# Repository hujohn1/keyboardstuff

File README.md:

4-key wired macropad powered with USB-C

v1: Jul 28, 2026
Changed resistors from 5k to 5.1k
Added status LED
Changed multiple global labels to net labels
Rewired WS2812s
Changed resistor and capacitor namings

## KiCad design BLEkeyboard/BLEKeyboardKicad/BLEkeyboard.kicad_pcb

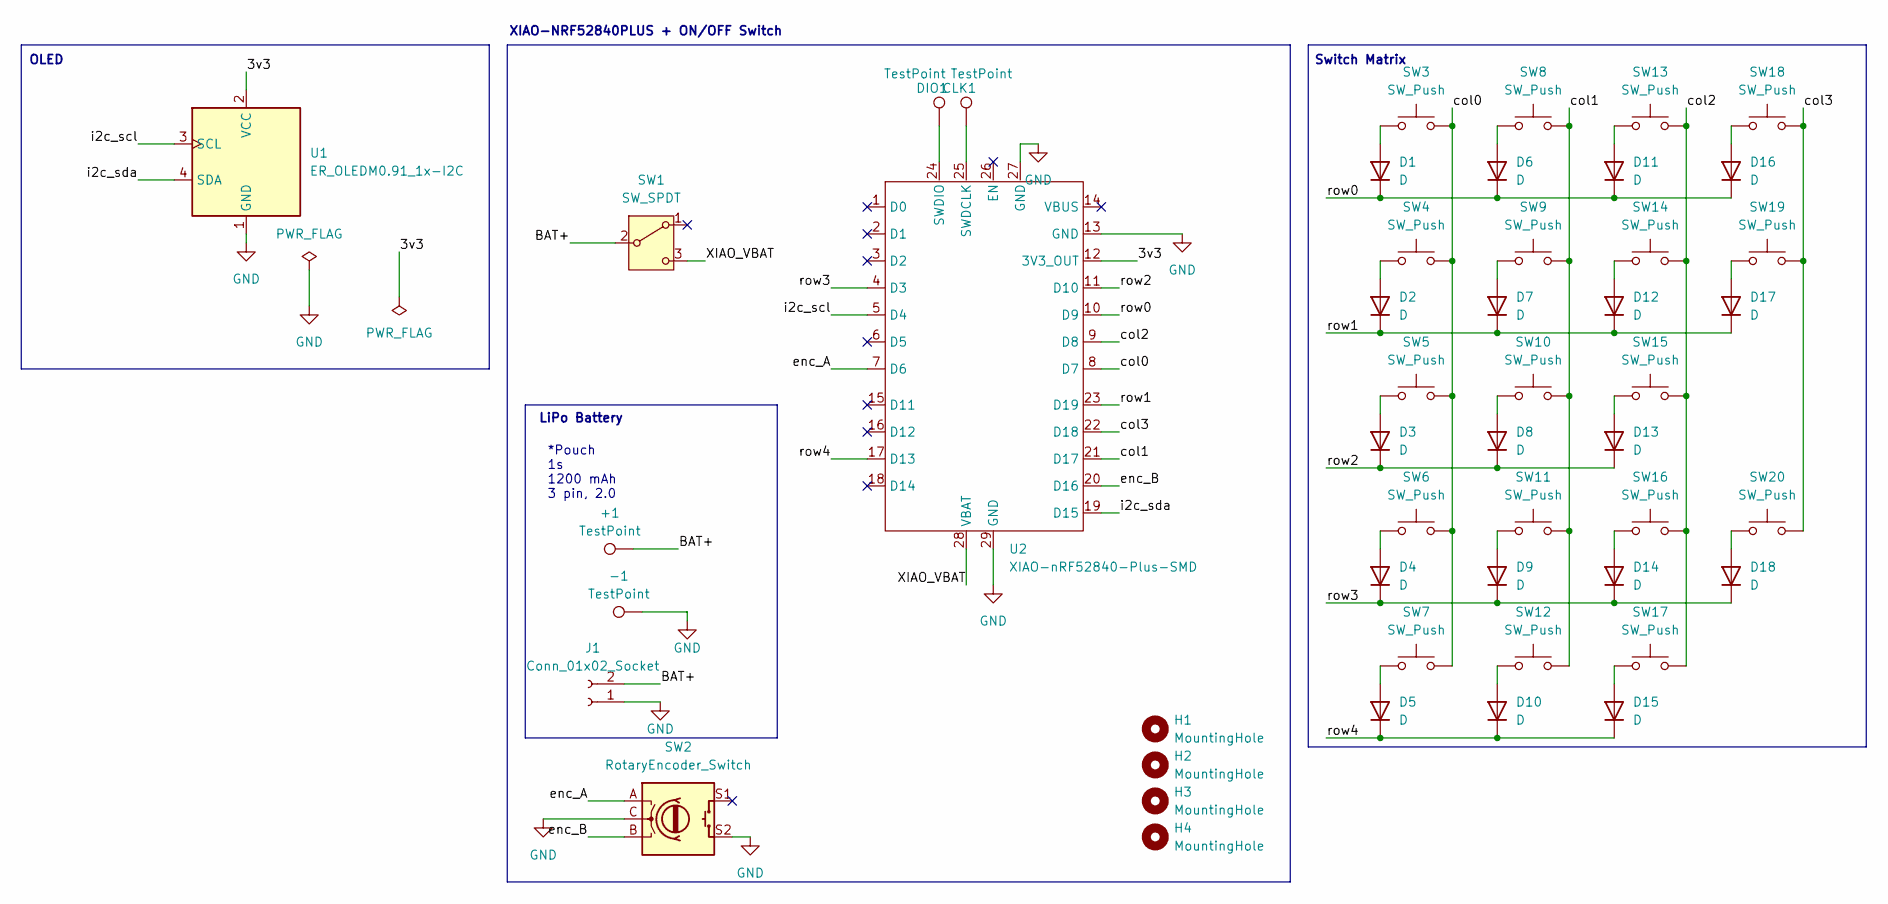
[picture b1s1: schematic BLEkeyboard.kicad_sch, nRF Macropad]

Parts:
+1: TestPoint; TestPoint_THTPad_D1.0mm_Drill0.5mm
-1: TestPoint; TestPoint_THTPad_D1.0mm_Drill0.5mm
CLK1: TestPoint; TestPoint_Pad_D2.0mm
D1, D2, D3, D4, D5, D6, D7, D8, D9, D10, D11, D12, D13, D14, D15, D16, D17, D18: D; D_DO-34_SOD68_P7.62mm_Horizontal
DIO1: TestPoint; TestPoint_Pad_D2.0mm
H1, H2, H3, H4: MountingHole; MountingHole_2.2mm_M2
J1: Conn_01x02_Socket; JST_PH_S2B-PH-K_1x02_P2.00mm_Horizontal
SW1: SW_SPDT; MK-12C02-G020_GSW
SW2: RotaryEncoder_Switch; RotaryEncoder_Alps_EC11E-Switch_Vertical_H20mm_MountingHoles
SW3, SW4, SW5, SW6, SW7, SW8, SW9, SW10, SW11, SW12, SW13, SW14, SW15, SW16, SW17, SW18: SW_Push; SW_Cherry_MX_PCB_1.00u
SW19, SW20: SW_Push; CherryMX_2.00u_PCB_StabWireBottom
U1: ER_OLEDM0.91_1x-I2C
U2: XIAO-nRF52840-Plus-SMD

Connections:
/3v3: U1.2 (VCC), U2.12 (3V3_OUT)
/BAT+: +1.1, J1.2, SW1.2 (B); also elsewhere on the board
/XIAO_VBAT: SW1.3 (C), U2.28 (VBAT)
/col0: SW3.2, SW4.2, SW5.2, SW6.2, SW7.2, U2.8 (D7)
/col1: SW8.2, SW9.2, SW10.2, SW11.2, SW12.2, U2.21 (D17)
/col2: SW13.2, SW14.2, SW15.2, SW16.2, SW17.2, U2.9 (D8)
/col3: SW18.2, SW19.2, SW20.2, U2.22 (D18)
/enc_A: SW2.A, U2.7 (D6)
/enc_B: SW2.B, U2.20 (D16)
/i2c_scl: U1.3 (SCL), U2.5 (D4)
/i2c_sda: U1.4 (SDA), U2.19 (D15)
/row0: D1.1 (K), D6.1 (K), D11.1 (K), D16.1 (K), U2.10 (D9)
/row1: D2.1 (K), D7.1 (K), D12.1 (K), D17.1 (K), U2.23 (D19)
/row2: D3.1 (K), D8.1 (K), D13.1 (K), U2.11 (D10)
/row3: D4.1 (K), D9.1 (K), D14.1 (K), D18.1 (K), U2.4 (D3)
/row4: D5.1 (K), D10.1 (K), D15.1 (K), U2.17 (D13)
GND: -1.1, J1.1, SW2.C, SW2.S2, U1.1 (GND), U2.13 (GND), U2.27 (GND), U2.29 (GND); also elsewhere on the board
unnamed: D1.2 (A), SW3.1
unnamed: D2.2 (A), SW4.1
unnamed: D3.2 (A), SW5.1
unnamed: D4.2 (A), SW6.1
unnamed: D5.2 (A), SW7.1
unnamed: D6.2 (A), SW8.1
unnamed: D7.2 (A), SW9.1
unnamed: D8.2 (A), SW10.1
unnamed: D9.2 (A), SW11.1
unnamed: D10.2 (A), SW12.1
unnamed: D11.2 (A), SW13.1
unnamed: D12.2 (A), SW14.1
unnamed: D13.2 (A), SW15.1
unnamed: D14.2 (A), SW16.1
unnamed: D15.2 (A), SW17.1
unnamed: D16.2 (A), SW18.1
unnamed: D17.2 (A), SW19.1
unnamed: D18.2 (A), SW20.1
unnamed 35: CLK1.1, U2.25 (SWDCLK); also elsewhere on the board
unnamed 36: DIO1.1, U2.24 (SWDIO); also elsewhere on the board

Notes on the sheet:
LiPo Battery
OLED
*Pouch 1s 1200 mAh 3 pin, 2.0
XIAO-NRF52840PLUS + ON/OFF Switch
Switch Matrix

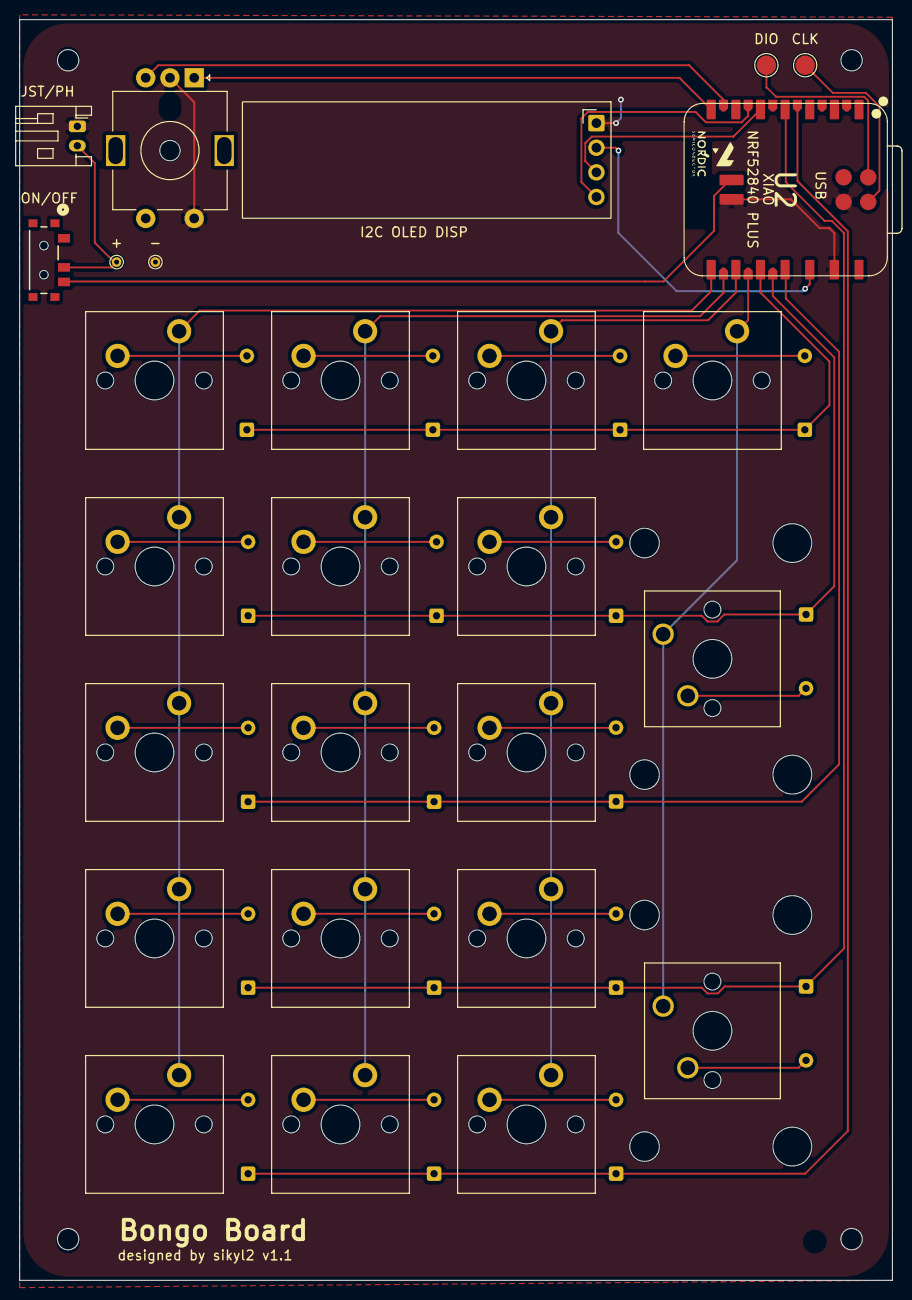
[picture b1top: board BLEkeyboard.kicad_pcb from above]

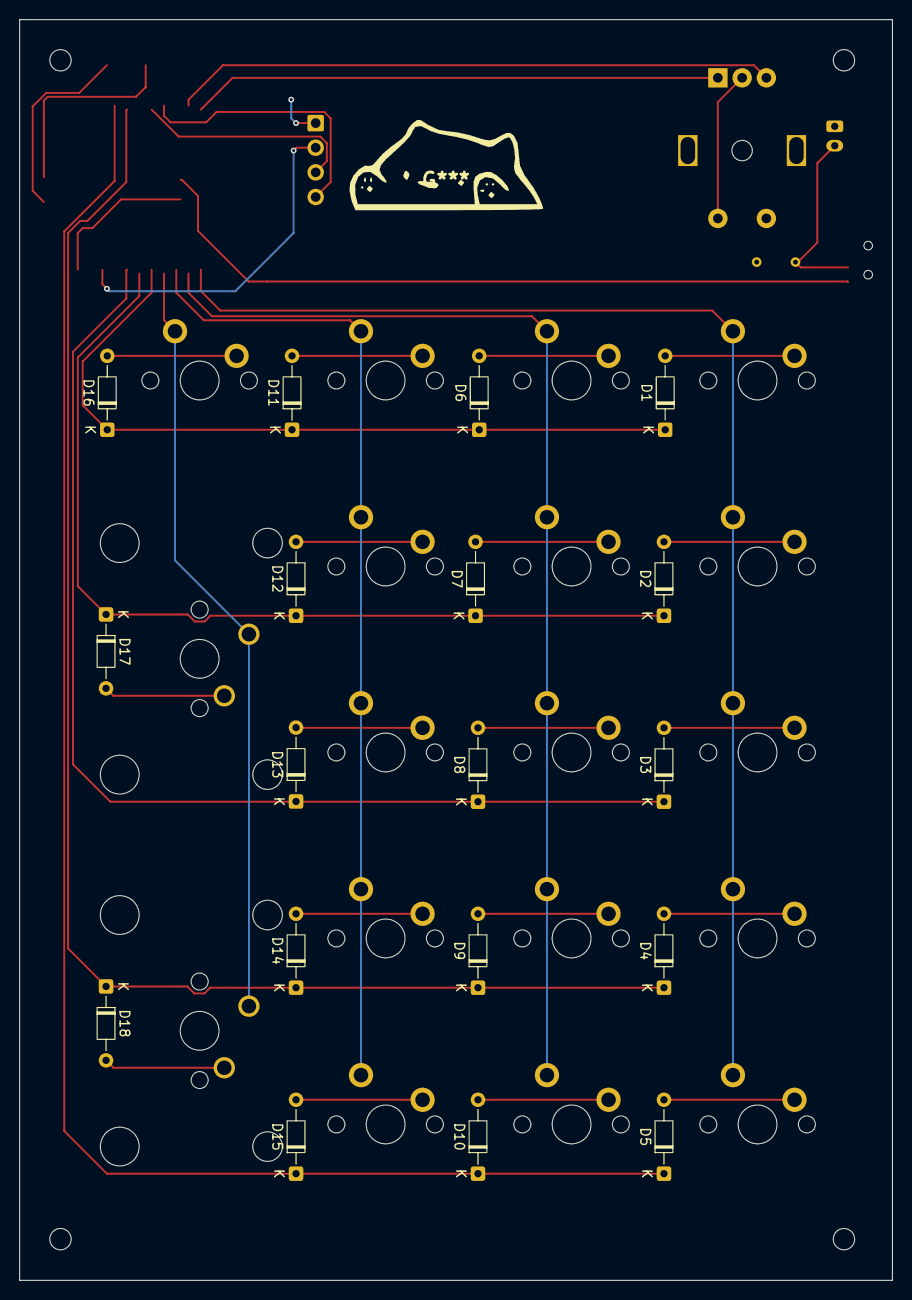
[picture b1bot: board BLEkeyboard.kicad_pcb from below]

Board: 2 copper layers, 90.0 x 130.0 mm, 50 parts (18 on the bottom side), 37 nets.

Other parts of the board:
': LOGO
+: TestPoint; TestPoint_THTPad_D1.0mm_Drill0.5mm
-: TestPoint; TestPoint_THTPad_D1.0mm_Drill0.5mm
CLK: TestPoint; TestPoint_Pad_D2.0mm
DIO: TestPoint; TestPoint_Pad_D2.0mm

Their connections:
/BAT+: +.1 (1_1); also elsewhere on the board
GND: -.1 (1_1); also elsewhere on the board
unnamed 35: CLK.1 (1_1); also elsewhere on the board
unnamed 36: DIO.1 (1_1); also elsewhere on the board

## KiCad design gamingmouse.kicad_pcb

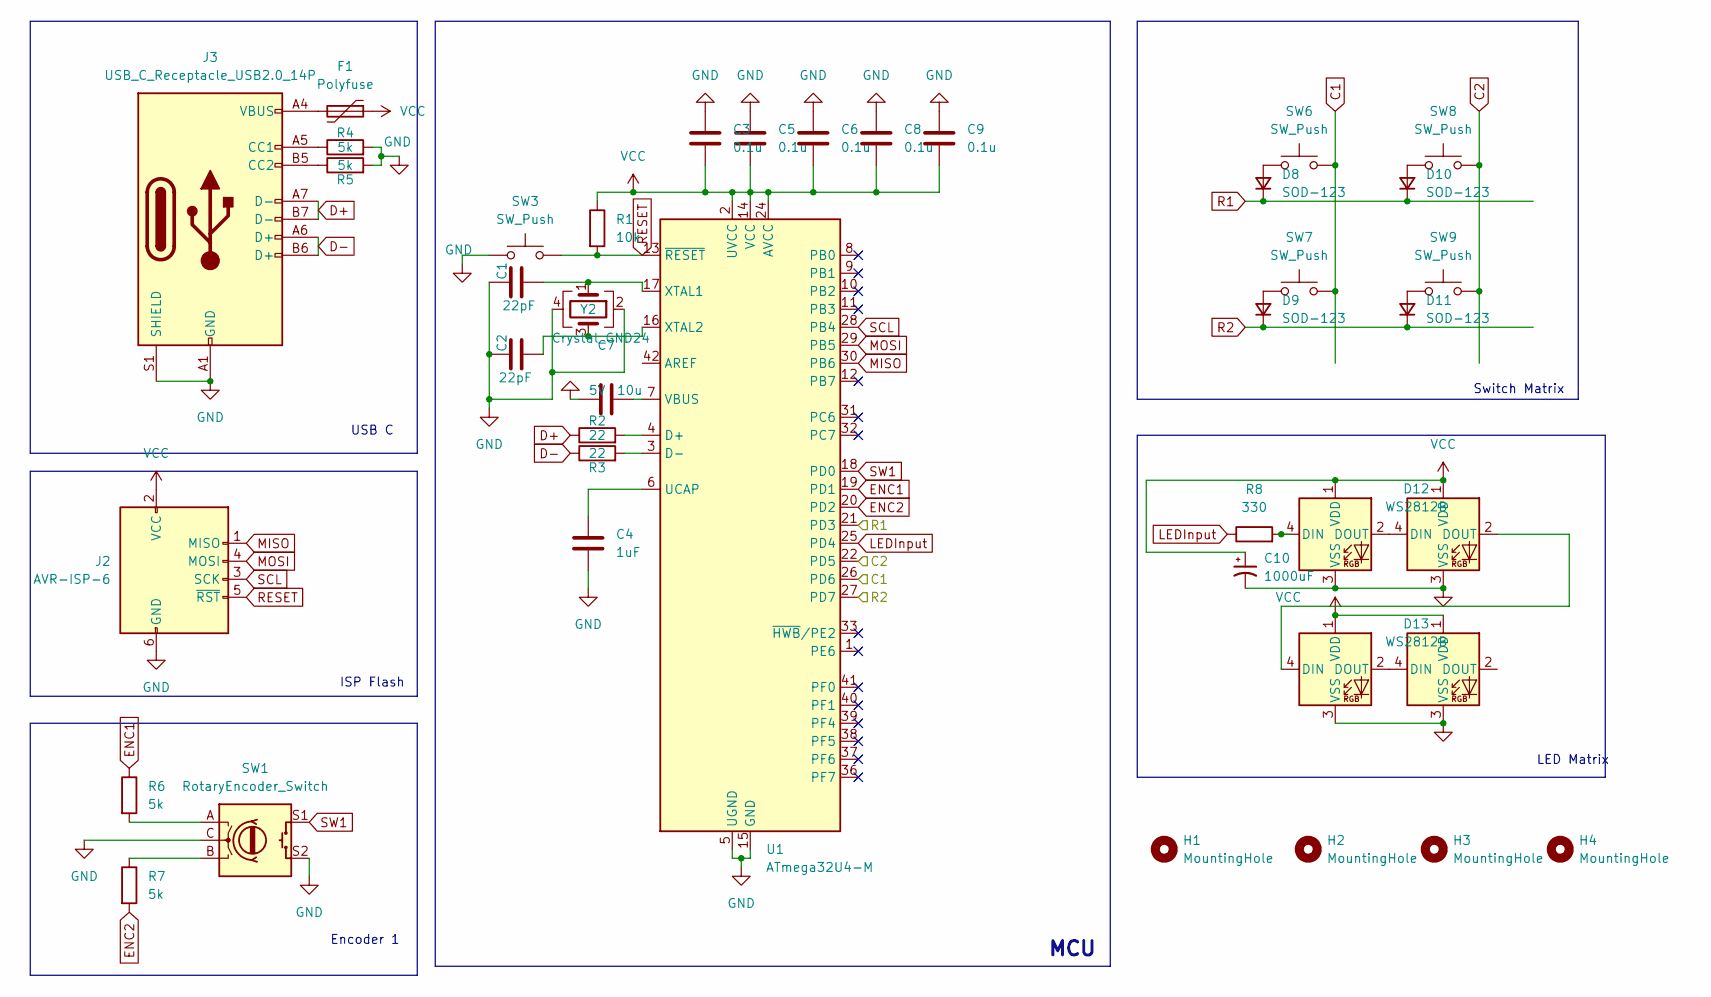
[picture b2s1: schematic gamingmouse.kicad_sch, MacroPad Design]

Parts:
C1, C2: 22pF; C_0805_2012Metric
C3, C5, C6, C8, C9: 0.1u; C_0805_2012Metric
C4: 1uF; C_0805_2012Metric
C7: 10u; C_0805_2012Metric
C10: 1000uF; CP_Elec_10x10
D8, D9, D10, D11: SOD-123; D_SOD-123
D12, D13, D14, D15: WS2812B; LED_WS2812B_PLCC4_5.0x5.0mm_P3.2mm
F1: Polyfuse; Fuse_1206_3216Metric
H1, H2, H3, H4: MountingHole; MountingHole_3mm
J2: AVR-ISP-6; Reset_Pretty-Mask
J3: USB_C_Receptacle_USB2.0_14P; USB_C_Receptacle_HRO_TYPE-C-31-M-12
R1: 10k; R_0805_2012Metric
R2, R3: 22; R_0805_2012Metric
R4, R5, R6, R7: 5k; R_0805_2012Metric
R8: 330; R_0805_2012Metric
SW1: RotaryEncoder_Switch; RotaryEncoder_Alps_EC11E-Switch_Vertical_H20mm
SW3: SW_Push; SW_PUSH_6mm
SW6, SW7, SW8, SW9: SW_Push; LED_MX_WS2812_2020
U1: ATmega32U4-M; QFN-44-1EP_7x7mm_P0.5mm_EP5.2x5.2mm
Y2: Crystal_GND24; Crystal_SMD_3225-4Pin_3.2x2.5mm

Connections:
5V: C7.1
C1: SW6.2, SW7.2, U1.26 (PD6)
C2: SW8.2, SW9.2, U1.22 (PD5)
ENC1: R6.1, U1.19 (PD1)
ENC2: R7.2, U1.20 (PD2)
GND: C1.1, C2.1, C3.1, C4.1, C5.1, C6.1, C8.1, C9.1, C10.2, D12.3 (VSS), D13.3 (VSS), D14.3 (VSS), D15.3 (VSS), J2.6 (GND), J3.A1 (GND), J3.A12 (GND), J3.B1 (GND), J3.B12 (GND), J3.S1 (SHIELD), R4.2, R5.2, SW1.C, SW1.S2, SW3.1, U1.5 (UGND), U1.15 (GND), U1.23 (GND), U1.35 (GND), U1.43 (GND), U1.45 (GND), Y2.2, Y2.4
LEDInput: R8.1, U1.25 (PD4)
MISO: J2.1 (MISO), U1.30 (PB6)
MOSI: J2.4 (MOSI), U1.29 (PB5)
unnamed: D8.2 (A), SW6.1
unnamed: D9.2 (A), SW7.1
unnamed: D10.2 (A), SW8.1
unnamed: D11.2 (A), SW9.1
unnamed: D12.4 (DIN), R8.2
unnamed: D12.2 (DOUT), D14.4 (DIN)
unnamed: D13.4 (DIN), D14.2 (DOUT)
unnamed: D13.2 (DOUT), D15.4 (DIN)
unnamed: F1.2, J3.A4 (VBUS), J3.A9 (VBUS), J3.B4 (VBUS), J3.B9 (VBUS)
unnamed: J3.A5 (CC1), R4.1
unnamed: J3.B5 (CC2), R5.1
unnamed: R6.2, SW1.A
unnamed: R7.1, SW1.B
unnamed: C4.2, U1.6 (UCAP)
unnamed: C7.2, U1.7 (VBUS)
unnamed: C1.2, U1.17 (XTAL1), Y2.1
unnamed: C2.2, U1.16 (XTAL2), Y2.3
R1: D8.1 (K), D10.1 (K), U1.21 (PD3)
R2: D9.1 (K), D11.1 (K), U1.27 (PD7)
RESET: J2.5 (~RST), R1.2, SW3.2, U1.13 (~RESET)
SCL: J2.3 (SCK), U1.28 (PB4)
SW1: SW1.S1, U1.18 (PD0)
VCC: C3.2, C5.2, C6.2, C8.2, C9.2, C10.1, D12.1 (VDD), D13.1 (VDD), D14.1 (VDD), D15.1 (VDD), F1.1, J2.2 (VCC), R1.1, U1.2 (UVCC), U1.14 (VCC), U1.24 (AVCC), U1.34 (VCC), U1.44 (AVCC)

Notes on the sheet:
Switch Matrix
USB C
MCU
ISP Flash
LED Matrix
Encoder 1

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
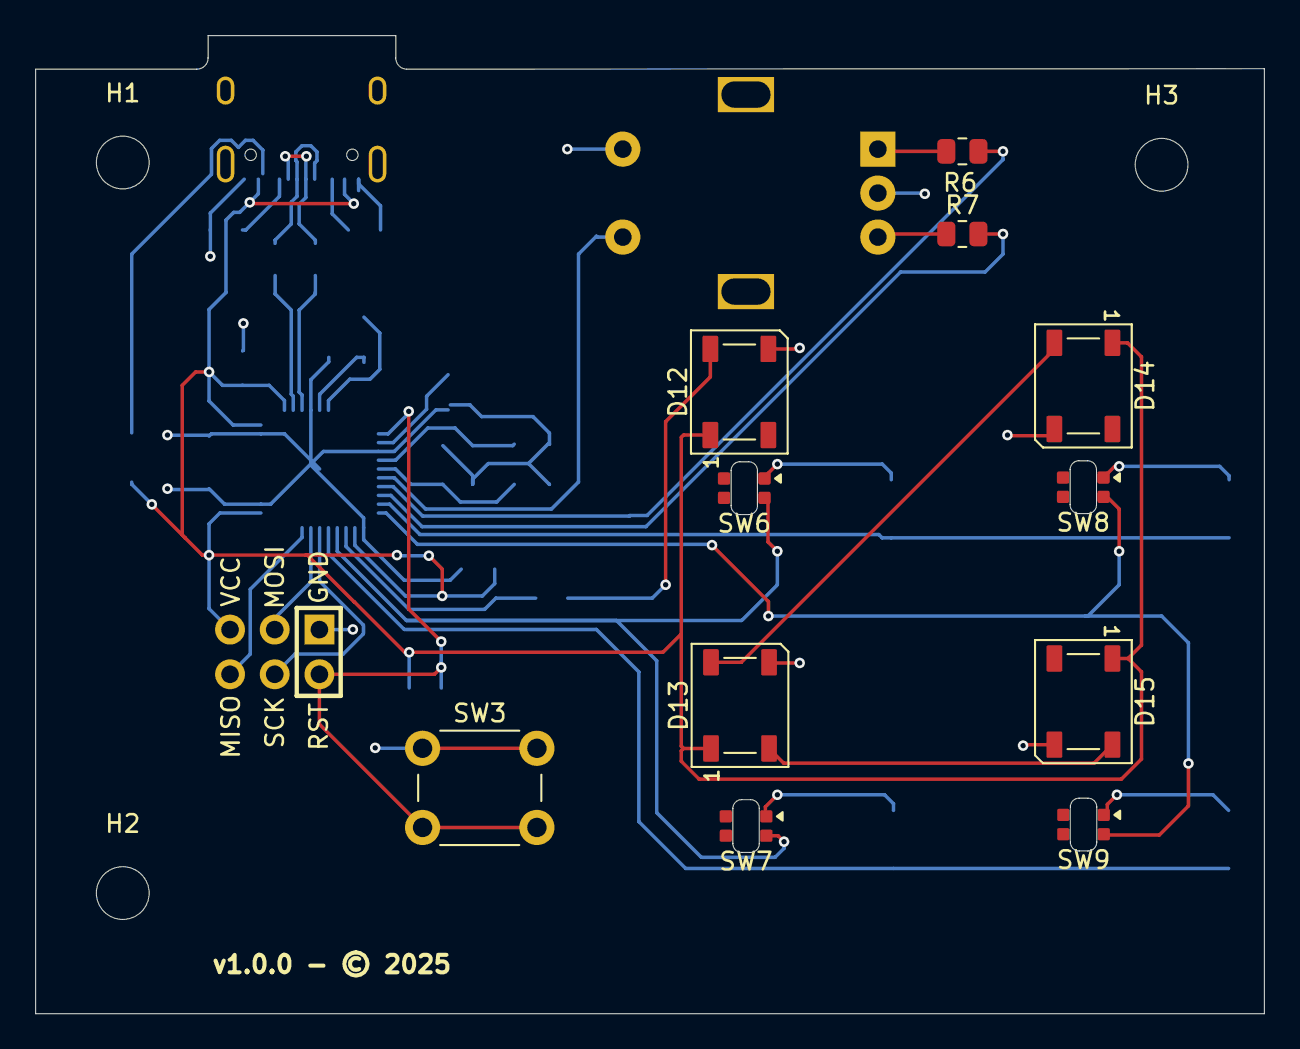
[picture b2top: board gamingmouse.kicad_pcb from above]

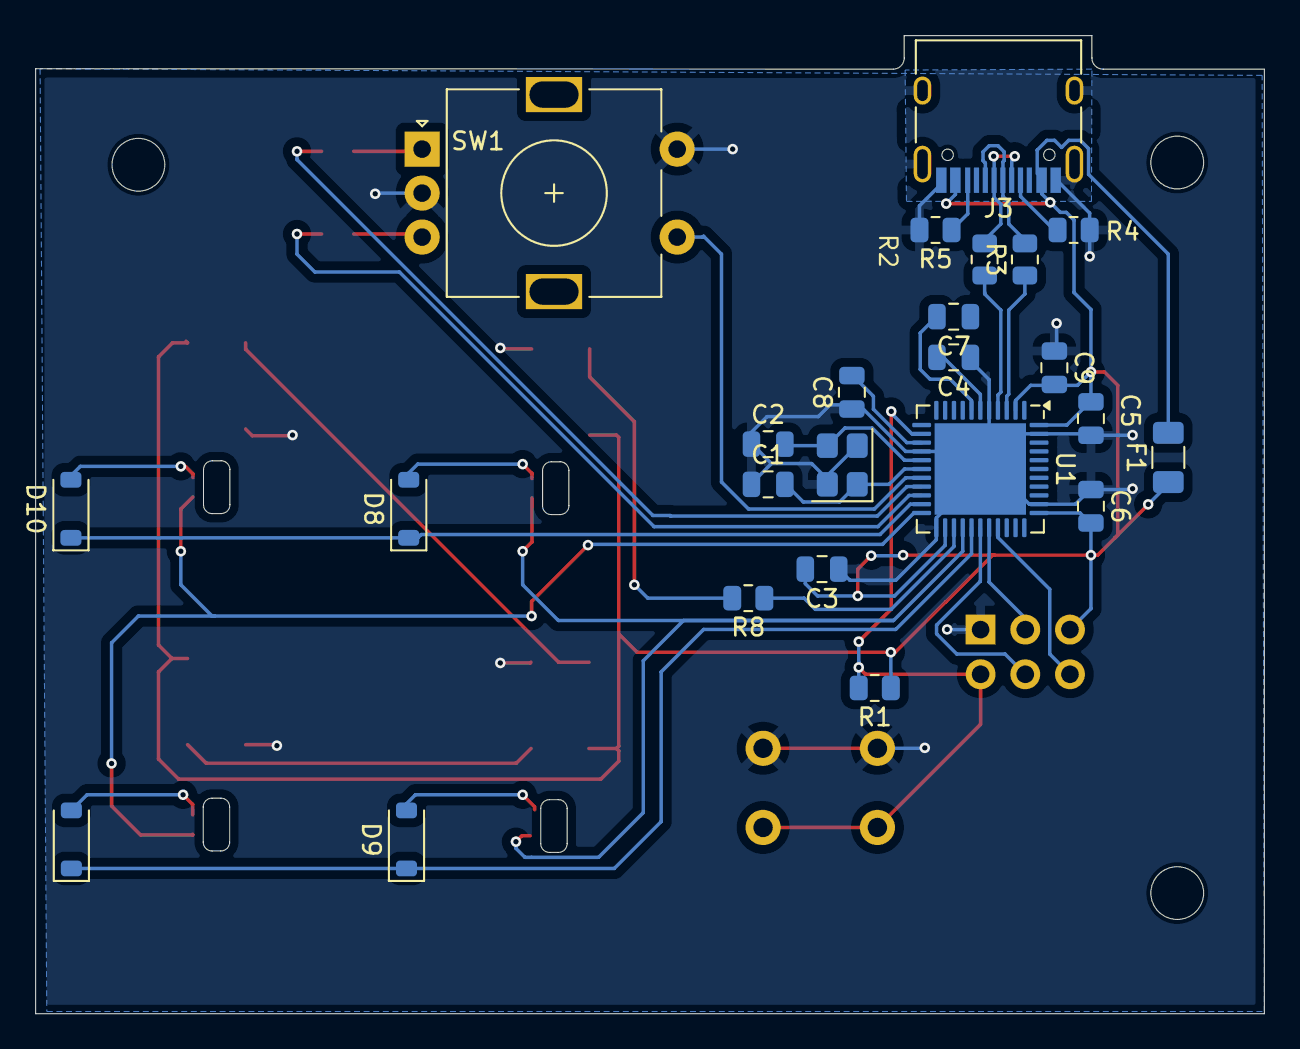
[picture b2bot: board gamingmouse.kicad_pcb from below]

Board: 2 copper layers, 69.9 x 55.6 mm, 39 parts (24 on the bottom side), 33 nets.

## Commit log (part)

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2025-11-18 initial backdated commit
2025-11-18 added README.md
2025-11-18 Fix image links in README.md
    Updated image links in README to point to GitHub.
2025-11-18 Fix image links in README for direct access
    Updated image links to include raw=true for direct access.
2025-11-18 Change image links to local paths
    Updated image links to local paths in README.md
2025-11-18 Fix image paths in README.md

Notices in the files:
gamingmouse.kicad_pcb:
v1.0.0 - © 2025
